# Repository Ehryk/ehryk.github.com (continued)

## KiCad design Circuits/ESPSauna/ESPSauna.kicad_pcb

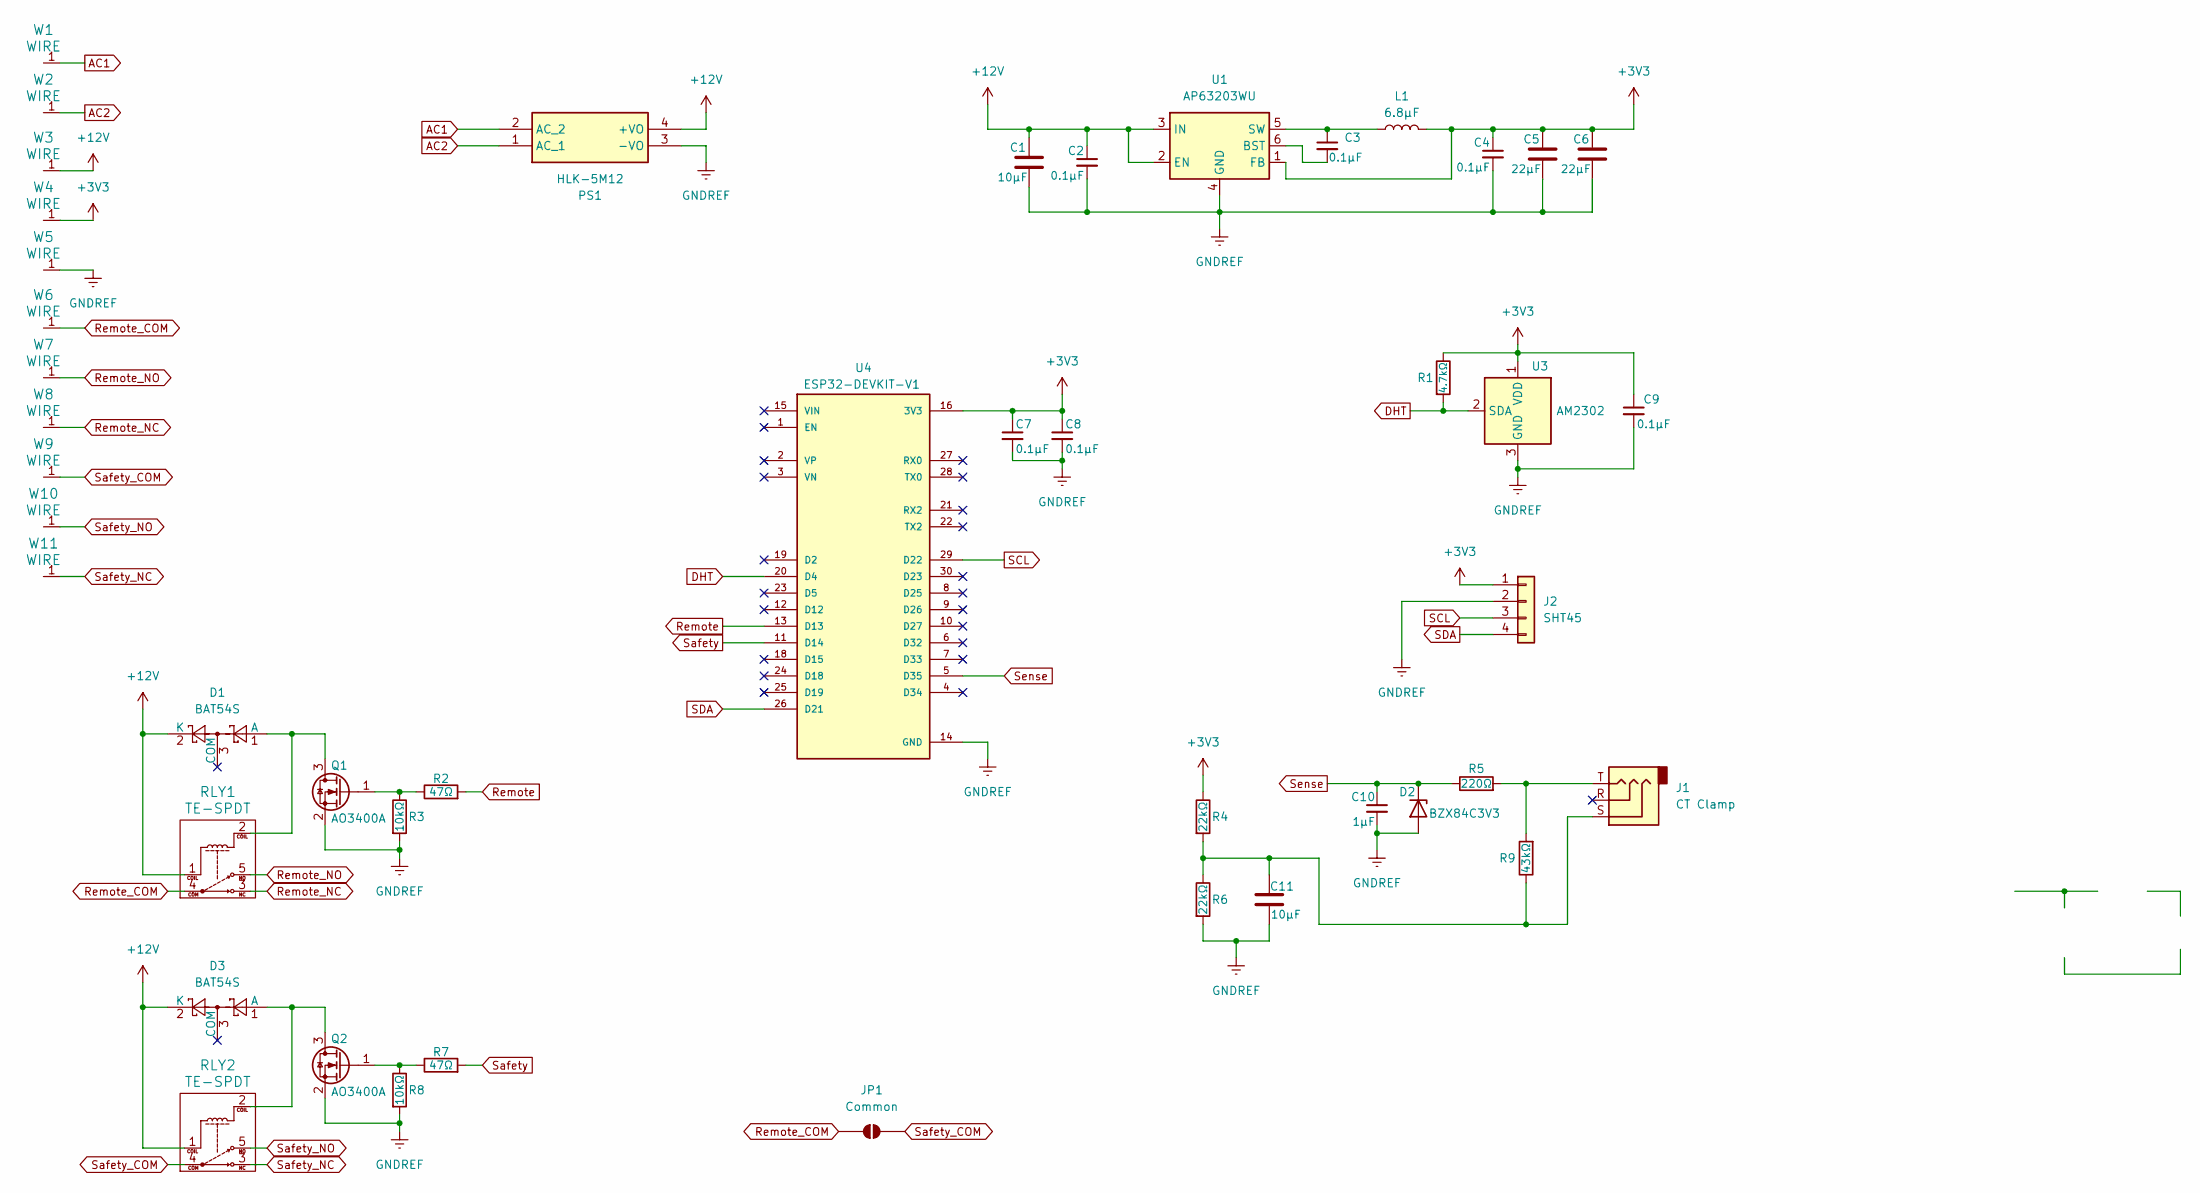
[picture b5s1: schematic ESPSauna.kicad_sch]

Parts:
C1, C11: 10μF; C_1206_3216Metric_Pad1.33x1.80mm_HandSolder
C2, C3, C4, C7, C8, C9: 0.1μF; C_0805_2012Metric_Pad1.18x1.45mm_HandSolder
C5, C6: 22μF; C_1210_3225Metric_Pad1.33x2.70mm_HandSolder
C10: 1μF; C_0805_2012Metric_Pad1.18x1.45mm_HandSolder
D1, D3: BAT54S; SOT-23
D2: BZX84C3V3; SOT-23
J1: CT Clamp; Jack_3.5mm_CUI_SJ1-3523N_Horizontal
J2: SHT45; PinSocket_1x04_P2.54mm_Vertical
JP1: Common; SolderJumper-2_P1.3mm_Open_RoundedPad1.0x1.5mm
L1: 6.8μF; L_Abracon_ASPI-0630LR
PS1: HLK-5M12; HLK5M12; Manufacturer_Part_Number HLK-5M12
Q1, Q2: AO3400A; SOT-23
R1: 4.7kΩ; R_0805_2012Metric_Pad1.20x1.40mm_HandSolder
R2, R7: 47Ω; R_0805_2012Metric_Pad1.20x1.40mm_HandSolder
R3, R8: 10kΩ; R_0805_2012Metric_Pad1.20x1.40mm_HandSolder
R4, R6: 22kΩ; R_0805_2012Metric_Pad1.20x1.40mm_HandSolder
R5: 220Ω; R_0805_2012Metric_Pad1.20x1.40mm_HandSolder
R9: 43kΩ; R_Axial_DIN0207_L6.3mm_D2.5mm_P10.16mm_Horizontal
RLY1, RLY2: TE-SPDT
U1: AP63203WU; TSOT-23-6
U3: AM2302; ASAIR_AM2302_P2.54mm_Vertical
U4: ESP32-DEVKIT-V1; ESP32_DEVKIT_V1
W1, W2, W3, W4, W5, W6, W7, W8, W9, W10, W11: WIRE; WIRE-18AWG

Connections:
+3V3: C4.1, C5.1, C6.1, C7.1, C8.1, C9.1, J2.1, L1.2, R1.1, R4.1, U1.1 (FB), U3.1 (VDD), U4.16 (3V3), W4.1
+12V: C1.1, C2.1, D1.2 (K), D3.2 (K), PS1.4 (+VO), RLY1.1, RLY2.1, U1.2 (EN), U1.3 (IN), W3.1
AC1: PS1.2 (AC_2), W1.1
AC2: PS1.1 (AC_1), W2.1
DHT: R1.2, U3.2 (SDA), U4.20 (D4)
GNDREF: C1.2, C2.2, C4.2, C5.2, C6.2, C7.2, C8.2, C9.2, C10.2, C11.2, D2.1 (A), J2.2, PS1.3 (-VO), Q1.2 (S), Q2.2 (S), R3.2, R6.2, R8.2, U1.4 (GND), U3.3 (GND), U3.4 (GND), U4.14 (GND), U4.17 (GND), W5.1
unnamed: C11.1, J1.S, R4.2, R6.1, R9.1
unnamed: D1.1 (A), Q1.3 (D), RLY1.2
unnamed: D3.1 (A), Q2.3 (D), RLY2.2
unnamed: J1.T, R5.2, R9.2
unnamed: Q1.1 (G), R2.1, R3.1
unnamed: Q2.1 (G), R7.1, R8.1
unnamed: C3.2, U1.6 (BST)
unnamed: C3.1, L1.1, U1.5 (SW)
Remote: R2.2, U4.13 (D13)
Remote_COM: JP1.1 (A), RLY1.4, W6.1
Remote_NC: RLY1.3, W8.1
Remote_NO: RLY1.5, W7.1
SCL: J2.3, U4.29 (D22)
SDA: J2.4, U4.26 (D21)
Safety: R7.2, U4.11 (D14)
Safety_COM: JP1.2 (B), RLY2.4, W9.1
Safety_NC: RLY2.3, W11.1
Safety_NO: RLY2.5, W10.1
Sense: C10.1, D2.3 (K), R5.1, U4.5 (D35)

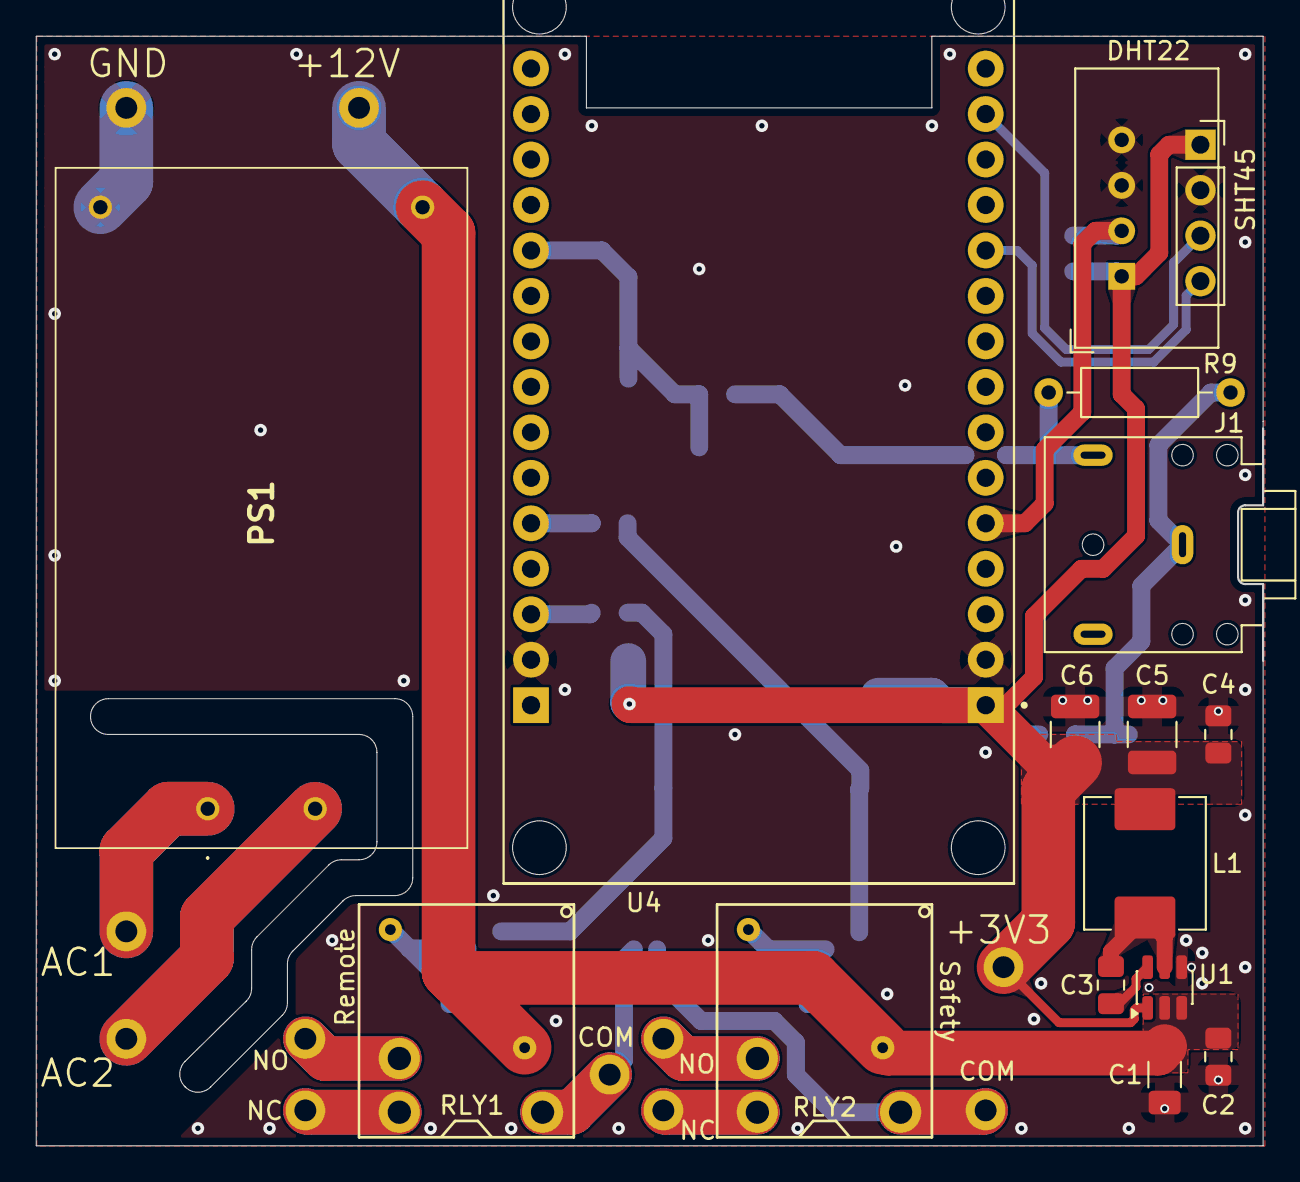
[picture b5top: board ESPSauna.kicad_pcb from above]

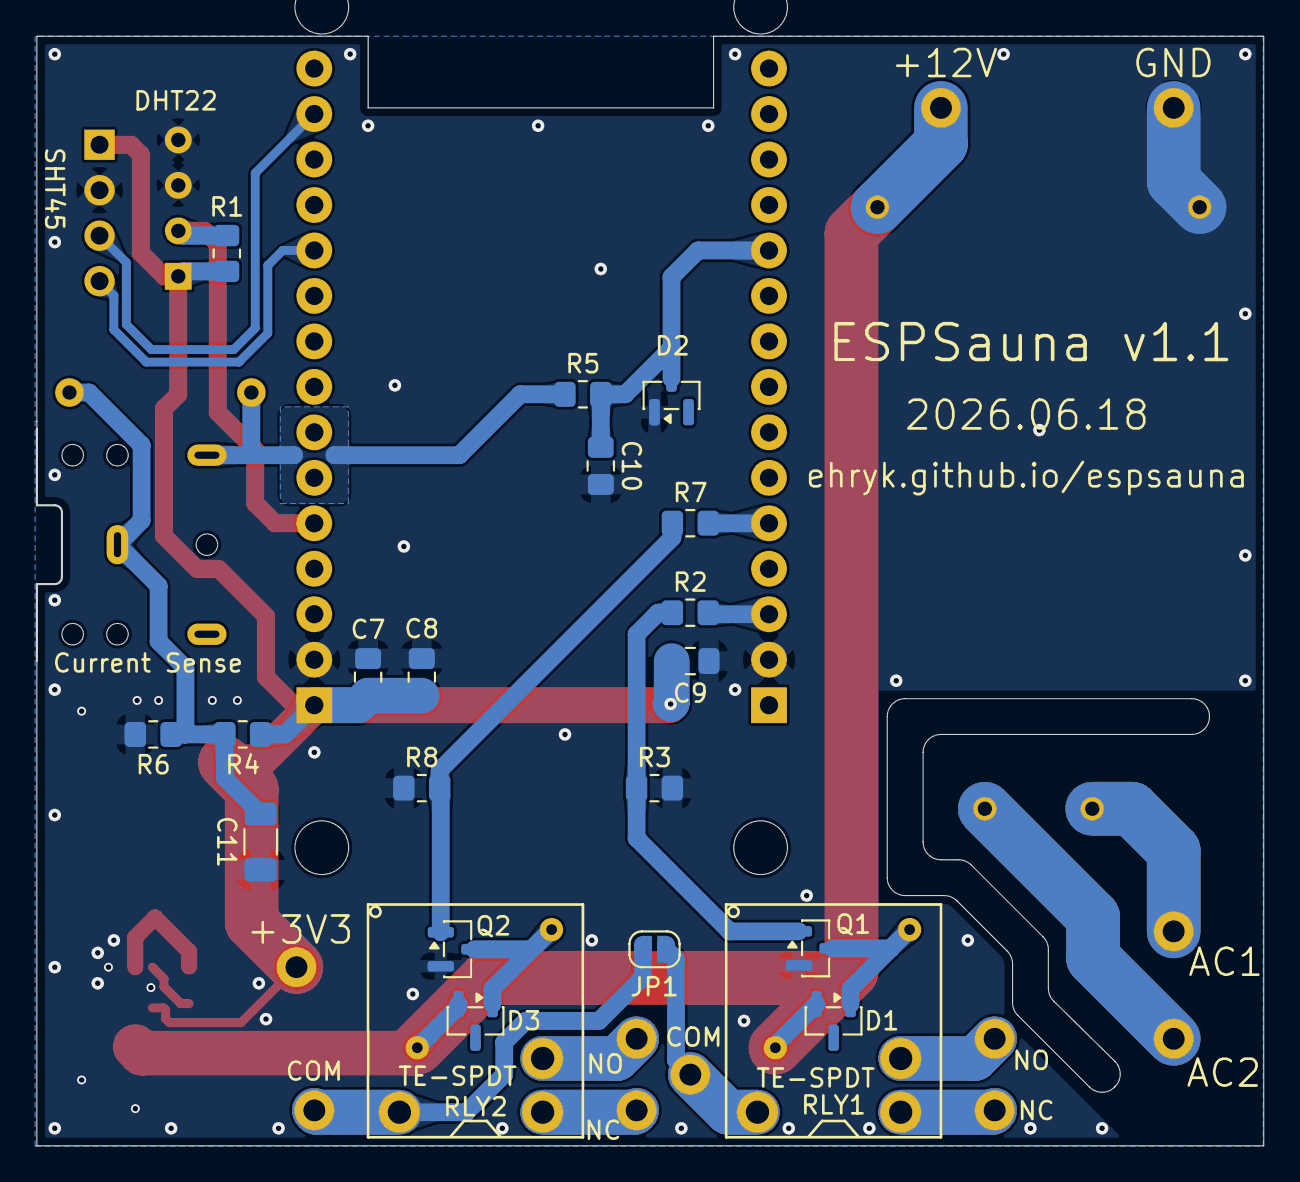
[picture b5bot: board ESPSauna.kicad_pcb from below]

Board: 2 copper layers, 68.5 x 61.9 mm, 46 parts (19 on the bottom side), 25 nets.

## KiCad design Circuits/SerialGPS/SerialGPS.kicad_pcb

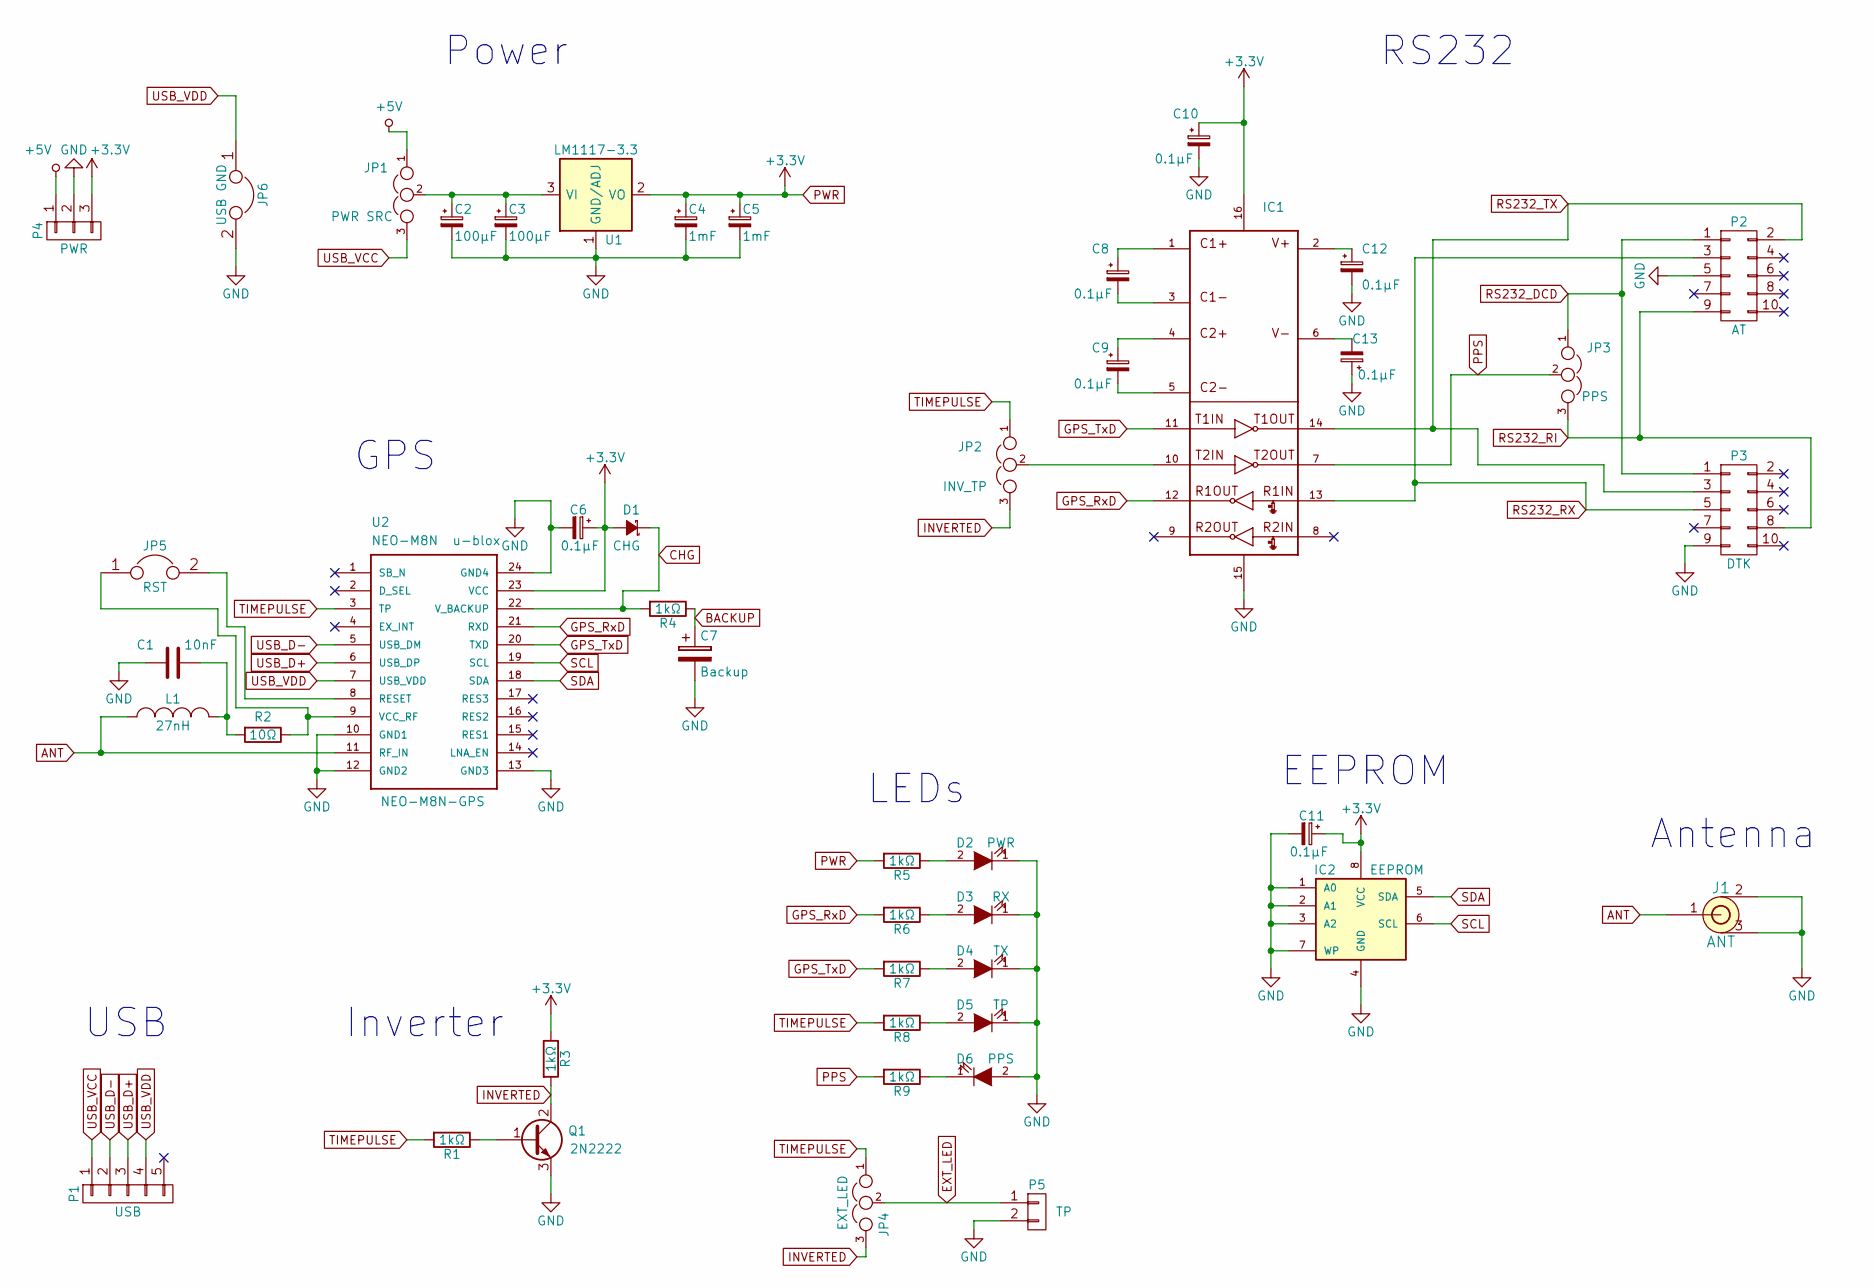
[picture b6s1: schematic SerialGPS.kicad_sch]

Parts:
C1: 10nF; C_1206_HandSoldering
C2, C3: 100µF; CP_Radial_D6.3mm_P2.50mm
C4, C5: 1mF; CP_Radial_D8.0mm_P5.00mm
C6, C8, C9, C10, C11, C12, C13: 0.1µF; C_1206_HandSoldering
C7: Backup; CP_Radial_D22.0mm_P10.00mm_SnapIn
D1: CHG; D_DO-35_SOD27_P7.62mm_Horizontal
D2: PWR; LED_0603_HandSoldering
D3: RX; LED_0603_HandSoldering
D4: TX; LED_0603_HandSoldering
D5: TP; LED_0603_HandSoldering
D6: PPS; LED_0603_HandSoldering
IC1: MAX3232; SO-16-N
IC2: EEPROM; SOIC-8-N
J1: ANT; U.FL-COAX
JP1: PWR SRC; Pin_Header_Straight_1x03_Pitch2.54mm
JP2: INV_TP; Pin_Header_Straight_1x03_Pitch2.54mm
JP3: PPS; Pin_Header_Straight_1x03_Pitch2.54mm
JP4: EXT_LED; GS3
JP5: RST; GS2
JP6: USB GND; GS2
L1: 27nH; Inductor_1212
P1: USB; Pin_Header_Straight_1x05_Pitch2.54mm
P2: AT; Pin_Header_Straight_2x05_Pitch2.54mm
P3: DTK; Pin_Header_Straight_2x05_Pitch2.54mm
P4: PWR; Pin_Header_Straight_1x03_Pitch2.54mm
P5: TP; Pin_Header_Straight_1x02_Pitch2.54mm
Q1: 2N2222; TO-92_Inline_Wide
R1, R3, R4, R5, R6, R7, R8, R9: 1kΩ; R_Axial_DIN0204_L3.6mm_D1.6mm_P7.62mm_Horizontal
R2: 10Ω; R_Axial_DIN0204_L3.6mm_D1.6mm_P7.62mm_Horizontal
U1: LM1117-3.3; SOT-223-3_TabPin2
U2: NEO-M8N; GPS24P-SMD-1.1-16X12.2MM

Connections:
+5V: JP1.1, P4.1
ANT: J1.1 (CENTER), L1.1, U2.11 (RF_IN)
BACKUP: C7.1, R4.1
CHG: D1.1 (K), R4.2, U2.22 (V_BACKUP)
EXT_LED: JP4.2, P5.1
GND: C1.1, C2.2, C3.2, C4.2, C5.2, C6.2, C7.2, C10.2, C11.2, C12.2, C13.1, D2.1 (K), D3.1 (K), D4.1 (K), D5.1 (K), D6.2 (A), IC1.15 (GND), IC2.1 (A0), IC2.2 (A1), IC2.3 (A2), IC2.4 (GND), IC2.7 (WP), J1.2, J1.3, JP6.2, P2.5, P3.9, P4.2, P5.2, Q1.3 (E), U1.1 (GND/ADJ), U2.10 (GND1), U2.12 (GND2), U2.13 (GND3), U2.24 (GND4)
GPS_RxD: IC1.12 (R1OUT), R6.2, U2.21 (RXD)
GPS_TxD: IC1.11 (T1IN), R7.2, U2.20 (TXD)
INVERTED: JP2.3, JP4.3, Q1.2 (C), R3.2
unnamed: C1.2, L1.2, R2.2
unnamed: C2.1, C3.1, JP1.2, U1.3 (VI)
unnamed: C8.1, IC1.1 (C1+)
unnamed: C8.2, IC1.3 (C1-)
unnamed: C9.1, IC1.4 (C2+)
unnamed: C9.2, IC1.5 (C2-)
unnamed: C12.1, IC1.2 (V+)
unnamed: C13.2, IC1.6 (V-)
unnamed: D2.2 (A), R5.1
unnamed: D3.2 (A), R6.1
unnamed: D4.2 (A), R7.1
unnamed: D5.2 (A), R8.1
unnamed: D6.1 (K), R9.1
unnamed: IC1.10 (T2IN), JP2.2
unnamed: JP5.1, R2.1, U2.9 (VCC_RF)
unnamed: JP5.2, U2.8 (RESET)
unnamed: Q1.1 (B), R1.1
PPS: IC1.7 (T2OUT), JP3.2, R9.2
PWR: C4.1, C5.1, C6.1, C10.1, C11.1, D1.2 (A), IC1.16 (VCC), IC2.8 (VCC), P4.3, R3.1, R5.2, U1.2 (VO), U1.4 (VO), U2.23 (VCC)
RS232_DCD: JP3.1, P2.1, P3.1
RS232_RI: JP3.3, P2.9, P3.8
RS232_RX: IC1.13 (R1IN), P2.3, P3.5
RS232_TX: IC1.14 (T1OUT), P2.2, P3.3
SCL: IC2.6 (SCL), U2.19 (SCL)
SDA: IC2.5 (SDA), U2.18 (SDA)
TIMEPULSE: JP2.1, JP4.1, R1.2, R8.2, U2.3 (TP)
USB_D+: P1.3, U2.6 (USB_DP)
USB_D-: P1.2, U2.5 (USB_DM)
USB_VCC: JP1.3, P1.1
USB_VDD: JP6.1, P1.4, U2.7 (USB_VDD)

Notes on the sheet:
EEPROM
Inverter
LEDs
USB
Antenna
Power
RS232
GPS

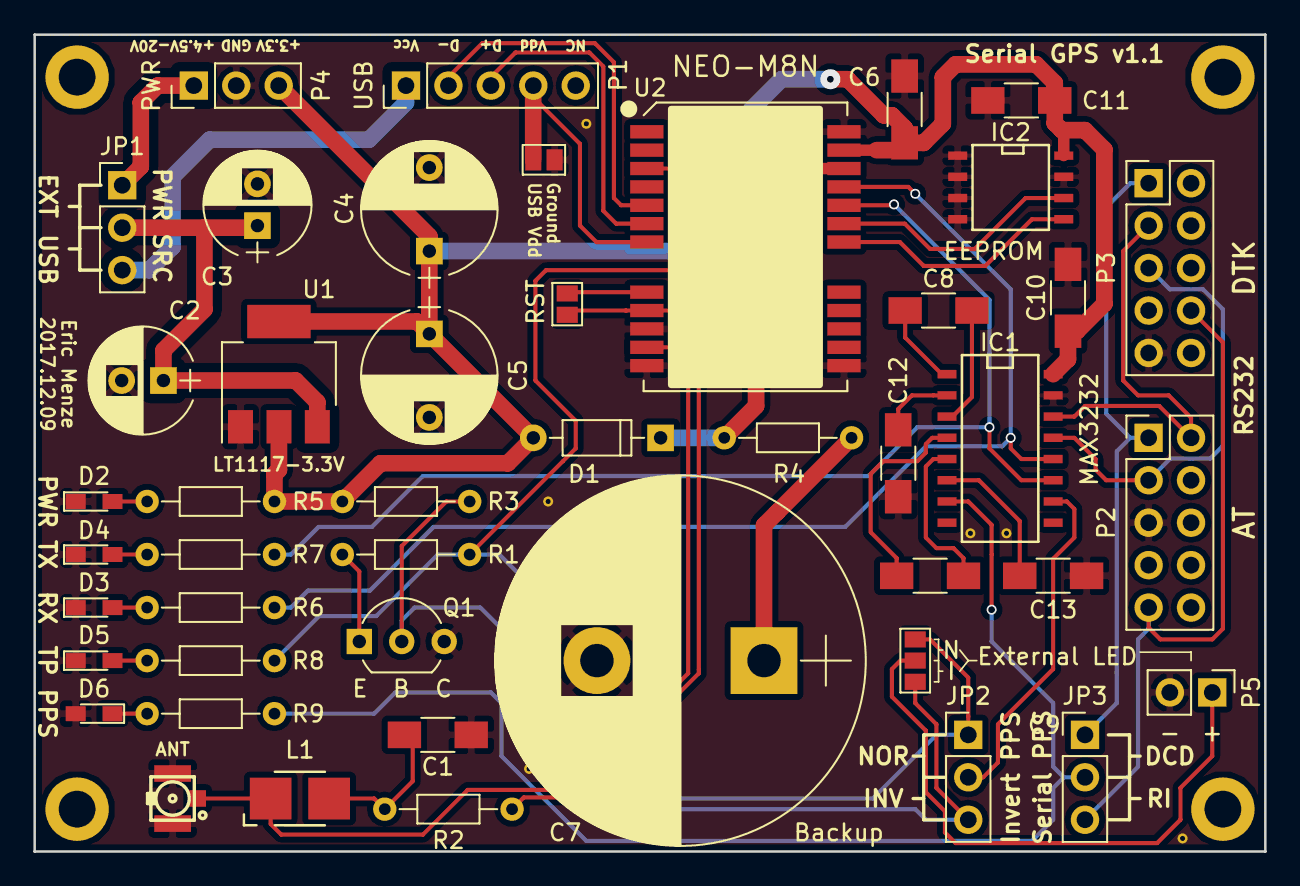
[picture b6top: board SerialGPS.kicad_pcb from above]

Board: 2 copper layers, 73.7 x 48.9 mm, 46 parts (0 on the bottom side), 39 nets.

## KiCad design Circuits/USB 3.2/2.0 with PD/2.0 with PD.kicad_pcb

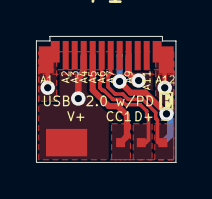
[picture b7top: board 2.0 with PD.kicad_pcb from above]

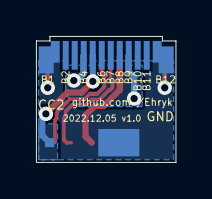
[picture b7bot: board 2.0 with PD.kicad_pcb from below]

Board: 2 copper layers, 7.8 x 7.0 mm, 7 parts (2 on the bottom side), 6 nets.

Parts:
P1: USB_C_Plug; USB_C_3.2
W1: V+; Pad
W2: CC1; Pad_Small
W3: CC2; Pad_Small
W4: D-; Pad_Small
W5: D+; Pad_Small
W6: GND; Pad

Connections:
/CC1: P1.A5 (CC), W2.1
/CC2: P1.B5 (VCONN), W3.1
/D+: P1.A6 (D+), W5.1
/D-: P1.A7 (D-), W4.1
/GND: P1.A1 (GND), P1.A12 (GND), P1.B1 (GND), P1.B12 (GND), W6.1
/Vbus: P1.A4 (VBUS), P1.A9 (VBUS), P1.B4 (VBUS), P1.B9 (VBUS), W1.1

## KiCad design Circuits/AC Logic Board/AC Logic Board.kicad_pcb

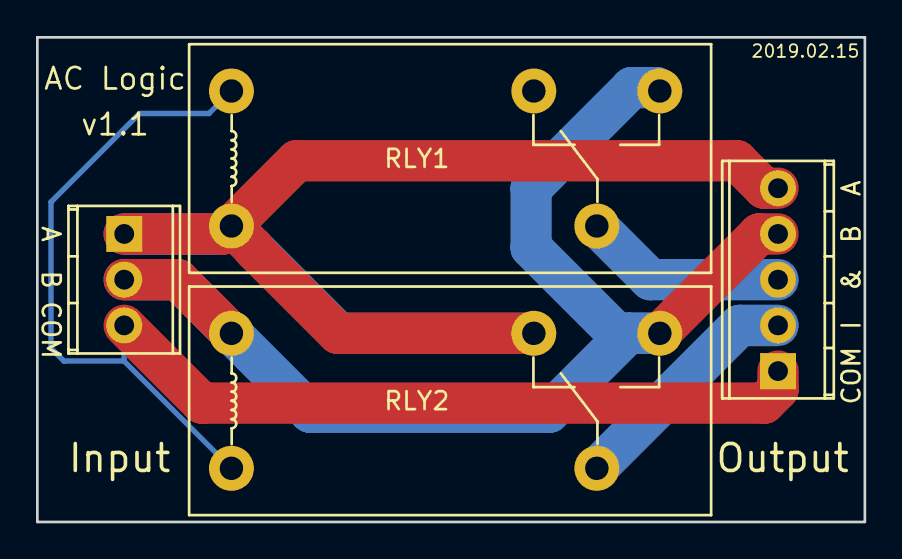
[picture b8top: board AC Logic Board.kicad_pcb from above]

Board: 2 copper layers, 46.0 x 26.9 mm, 4 parts (0 on the bottom side), 5 nets.

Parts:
J1: Input; TerminalBlock_Phoenix_MPT-2.54mm_3pol
J2: Output; TerminalBlock_Phoenix_MPT-2.54mm_5pol
RLY1: A; TE-RT1-3.5mm
RLY2: B; TE-RT1-3.5mm

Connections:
A: J1.1, J2.5, RLY1.A2, RLY2.12
AND: J2.3, RLY1.11
B: J1.2, J2.4, RLY1.14, RLY2.14, RLY2.A1
COMMON: J1.3, J2.1, RLY1.A1, RLY2.A2
OR: J2.2, RLY2.11

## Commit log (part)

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2011-12-09 Added CNAME record
2011-12-09 Fixed cname
2012-02-29 Added BigTextBox sample
2012-03-01 Readding CNAME
2013-02-20 Added linux helpers and config files
2013-02-20 Added tarball alias
2013-02-20 Added copy and rn aliases
2013-02-20 Added update-prefs.sh
2013-02-20 Root users show in red
2013-02-20 Fixed syntax error
2013-02-20 Updated aliases, added brian directory
2013-02-21 Working on login script, added .gitignore
2013-02-21 removed some stuff from automate_ge_ftp... First commit with VIM-Commands.pdf
2013-02-21 Misc. notes while figuring out bash
2013-02-21 Netcat examples for creating and listening for TCP connections. fm is a utility so I don't have to login to a system to move files around
2013-02-21 Adding /git directory for git prefs
2013-02-26 Added automate_ge_ftp
    (Cleaned)
2013-02-26 Adding Cygwin aliases
2013-02-26 Removing CNAME link to code.ehryk.com
2013-02-26 Starting Windows .bat scripts
2013-06-24 Added custom Rainmeter skins
2013-07-08 Added License (BSD)
2013-09-25 Fixed Windows Update Config.bat
    Added CygWin copy if found at C:\cygwin
2013-09-25 Windows Created a script to make a startup file in the UserProfile of the user running it
2013-09-25 Added an alias for git add with xargs
2013-10-05 Adding .gitattributes file to specify lf line endings in certain files
2013-10-25 Added gitconfig and gitk to sync process
2013-10-25 Updated .gitconfig to add more aliases
2013-10-26 Updating .gitk and .gitconfig in linux
2013-11-01 Chmod +x On the .sh files
2013-11-13 Adding Grey paneling and xkcd the News bookmarklet
2013-11-13 Updating site with css and js directories, favicon, etc.
2013-11-13 Adding OG image
2014-01-27 Added README
2014-01-31 Adding git lines alias
2014-03-17 Updating gitconfig: Adding new aliases (cam, ll, etc.) and updating lines/linecount aliases to work better
2014-04-07 Updating linux configs to fix issues with Git for Windows 1.9
2014-06-12 Added pik sourcing to .bashrc
2014-07-11 Added git aliases: addpattern, ignore, ap, apc, ar
2014-07-25 Added install_config to only copy the files, not clone and update the project to ~/Projects
2014-08-06 Added sequence.html to test something with alliesaurus
2014-08-06 Updating sequence styling
2014-08-20 Added mike as joke site
2014-08-20 bashrc line ending differences
2014-08-20 Editing mike site
2014-08-20 Editing Mike
2014-08-20 Mike: adding dynamic background swapping
2014-08-20 Mike: Added dial
2014-08-20 Mike: added new content for dial
2014-09-29 Added Chuck Missler markdown document
2014-09-29 Added line ending to Chuck Missler document
2014-09-29 Updated Chuck Missler document structure
2014-09-30 Formatting updates to OnChuckMissler
2014-09-30 More formatting updates to OnChuckMissler
2014-09-30 More OnChuckMissler updating
2015-01-08 Added EpochFail/name-js to /name-js
2015-01-08 Making header link to wutjs.com
2015-01-08 Making header link to wutjs.com white
2015-01-08 Using Carter's linode for data by IP address
2015-01-08 Making header link to wutjs.com not underlined
2015-01-08 Using Carter's linode for data by IP addres
2015-01-08 Uppercasing Word and Rating properties
2015-01-09 Further fixing name-js url and standardizing do-it.js indentation
2015-01-09 Additional word -> Word and rating -> Rating fixes
2015-01-09 Added name-js and mike to index page
2015-01-09 Updating link colors and alternating sections
2015-09-14 Added KeypressValidation example
2015-09-14 Updates to KeypressValidation
2015-09-24 Added Fritzing Crossovers
2015-09-26 Added attenuation switches and made PCB square
2015-10-04 Crossovers:Added Schematic Image
2015-10-05 Crossovers: Ordering PCB (v2)
2015-10-05 Crossovers: Added v3 with Phase Switches and bypass SPDT
2015-10-12 Added image of schematic v3
2015-11-12 Added AdapterStatus.bat v1.0
2015-11-13 Added AAA Cap Board, renamed /Crossovers -> /Audio
2015-11-16 Power Supply: Added KiCad project and datasheets
2015-11-17 Added Home System schematic and parts
2015-11-21 Power Supply: Added .pdf export of schematic
2015-11-21 Audio: Added Test project for small designs
2015-11-21 Audio: Added Notes
2015-11-21 Renamed Power Supply => Linear Power Supply
2015-11-21 Renamed Audio => Circuits
2016-01-14 Circuits: Added AAA cap board PCB Exports
2016-01-14 Added Pragmatic Programmer chapter 1 notes
2016-02-04 Adding PP Chapter 2 notes, incomplete
2016-02-04 Renaming image
2016-02-04 Updating image link
2016-03-10 Notes: Adding Pragmatic Programmer Chapter 3
2016-05-05 Added chapter 5 notes
2016-05-06 Adding Xaser motd.tcl
2016-05-19 Notes: Added PP ch. 6
2016-05-26 Fixed login display
2016-05-26 Added PP Chapter 7 notes
2016-05-29 Using pacman for update alias
2016-05-29 Adding ArchHP motd script
2016-06-02 Notes: Added PP Chapter 8 notes
2016-12-01 Circuits: Moving Kicad Parts to a common directory
2016-12-01 Circuits: Adding Kicad variant of the Crossover
2016-12-01 Circuits: Adding Transformer Breakout
2016-12-01 Circuits: Adding Garage Assistant (temp title)
2016-12-01 Circuits: Small updates to Transformer Breakouts: circle icon, removing thermal rings
2016-12-01 Circuits: Consolidating parts into singular library (ehryk.lib)
2016-12-05 Circuits: Readding av library
2016-12-05 Circuits: Updated 3d models on LPAD
2016-12-05 Circuits: Updating AAA Cap Board PCB
2016-12-05 Circuits: Updated 3d models on Garage Assistant
2016-12-21 Circuits: Updating X+ - reducing via count, updating resistor footprints
2016-12-21 Circuits: Updating text on Transformer Breakout
2017-03-29 linux: Adding motd script from ArchHP
2017-03-30 linux: Updating motd to use proper pronoun agreement
2017-03-31 img: Added TriumphTT600.jpg
2017-03-31 Added nope.html
2017-04-07 Added real.html
2017-08-18 Added DeTrumpify bookmarklet
2017-12-09 Mike: css change only
2017-12-09 AAA Cap Board: Edits?
2017-12-11 LPAD: Restructuring, producing Gerber export for fabrication
2017-12-11 SerialGPS: Initial commit of Kicad project
2017-12-15 Circuits: Adding X+ Images
2017-12-15 Circuits: Adding SerialGPS Images
2018-03-17 Added Parts: TE Relay and Wire Pads
2018-03-18 Parts: Fixing SPST and SPDT relays
2018-03-18 SerialGPS: Added documentation
2018-03-18 Transformer Breakout: breaking out into Planar and Parallel versions
2018-03-18 Home System: minor updates
2018-03-18 Garage Assistant: Updating
2018-07-11 Circuits: fixing hole diameter in relays
2018-07-13 Circuits: Added Adafruit Feather nRF52
2018-07-13 Circuits: Updated TE Relay and Wire parts
2018-07-13 Circuits: Added TEST, updated Feather nRF52
2018-07-14 Circuits: Minor updates
2018-07-16 Circuits: Adding Logos
2018-07-16 SerialGPS: Minor Updates
2018-07-16 LPAD: Adding Simulation, v0.1 Export
2018-08-04 Updating Wire Holes to accommodate TXL wire better
2019-02-05 Parts: Adding TE RT1 Relay library and footprint
2019-02-05 Circuits: Adding AC Logic Board
2019-02-05 CircuitsL Added TE RT1 Datasheet
2019-02-15 AC Logic Board: differentiating AC Logic Board and a Pro version
2019-04-08 Adding Past Tense bookmarklet
2019-04-08 Updating Past Tense Bookmarklet
2019-04-08 Adding image for past-tense bookmarklet
2019-10-24 Circuits: Adding parts for PSU Breakout
2019-10-24 Circuits: Adding Common Slot PSU Card
2019-10-30 PSU Breakout: Arranging in mini form factor
2019-11-05 Parts: Added M2.5 Screw and Standoff Holes
2019-11-05 Common Slot: Added v2 (Mounting hole variant)
2021-05-17 Mike: Updated jquery-ui.css
2021-05-17 Mike: Updated jquery-ui.min.js
2021-05-17 Mike: Added favicon.ico
2021-06-22 docs: Added RV Trip planning
2021-06-22 Updates to Trip Itinerary
2021-06-22 Added planner link:
2021-06-22 Fixed typo
2021-06-23 Starting reservations
2021-06-28 Updates to Trip Plan
2021-06-29 Updating Trip Itinerary
2021-07-06 Updating Bird West Progress
2021-07-08 Bird West plan updates
2021-07-17 Updating BirdWest trip info
2021-07-19 Updating BirdWest
2021-07-28 BirdWest actual itenerary update
2021-07-31 More updates from Eric
2021-09-20 Fixing past tense bookmarklet
2022-08-29 Circuits: Added Common Slot PSU Mini variant (no 5V output)
2022-08-29 Circuits: Updated AC Logic Board (images, typo)
2022-08-29 Circuits: Parts Updates
2022-11-13 Circuits: Added USB 3.2 Charger Breakout
2025-01-18 CAD: Added GBS-C Case
2026-05-01 Added Parts
2026-05-01 Working on USB 3.2
2026-05-01 Working on Serial GPS
2026-05-01 Working on LPAD Crossover
2026-05-01 Working on Common Slot PSU
2026-05-01 Working on Garage Assistant
2026-05-01 Added ESPDrive
2026-05-01 Updated ESPDrive Schematic
2026-05-02 Ignoring KiCAD backups directories
2026-05-02 ESPDrive: fixed regulator pad errors, small tweaks
2026-05-02 ESPDrive: Added exports
2026-05-02 ESPDrive: altered directory structure
2026-05-05 ESPDrive: Final tweaks before manufacture
2026-05-05 ESPDrive: Added exports for review (PDF) and manufacture (v1.0)
2026-05-05 ESPDrive: Added BOM
2026-05-05 Ignoring *.lck file (KiCAD 10 lock files)
2026-05-05 ESPDrive: Slight tweaks, added ordered parts to BOM
2026-05-07 ESPDrive: Added p channel mosfet to voltage divider; versioned to v1.1
2026-05-12 ESPDrive: small tweaks to silkscreens
2026-05-18 ESPDrive: Added teardrops
2026-05-26 ESPDrive: Finished update to v1.1
2026-05-26 ESPSauna: Added v1.0
2026-05-26 Removing local jquery/bootstrap/modernizr files, using CDN references
2026-06-18 Added fertilizer calculator
2026-06-18 Updates to fertilizer calculation
2026-06-18 Added parts for circuit projects
2026-06-18 Updates to ESPSauna (fixing current clamp)
2026-06-18 Updated ESPDrive BOM
2026-06-18 Added ESPFridge project
2026-06-18 Added ESPProbe project
2026-06-18 Added ESPRadiator project
2026-06-18 Updates to Fertilator
2026-06-18 Added changes in fertilator (new title)
2026-06-18 Added redirect, more refinements to fertilator
2026-06-18 Added weekly breakdown
2026-06-18 Fertilator: Added differential row
2026-06-18 Minor tweaks to Fertilator (page title)
2026-06-18 Added espsauna html page, added images
2026-06-19 Added ESPFridge intro page
2026-06-19 Added image opening full screen to index page
2026-06-19 Updating index.html
2026-06-19 Overhaul of html pages; pulling out js and css into separate files, using no image fallback, adding espprobe, espdrive and espradiator stubs awaiting images
2026-06-19 Made the section headers links
2026-06-19 Added ESP images; added sections to index.html
2026-06-19 Added yaml files for ESP projects
2026-06-22 Added images, updating ESP project pages
2026-06-22 Slight tweaks to project pages
2026-06-22 Updated espkey image, ESPDrive yaml
2026-06-22 Updated project summaries
2026-06-23 ESPFridge Fab layer and bom updates
